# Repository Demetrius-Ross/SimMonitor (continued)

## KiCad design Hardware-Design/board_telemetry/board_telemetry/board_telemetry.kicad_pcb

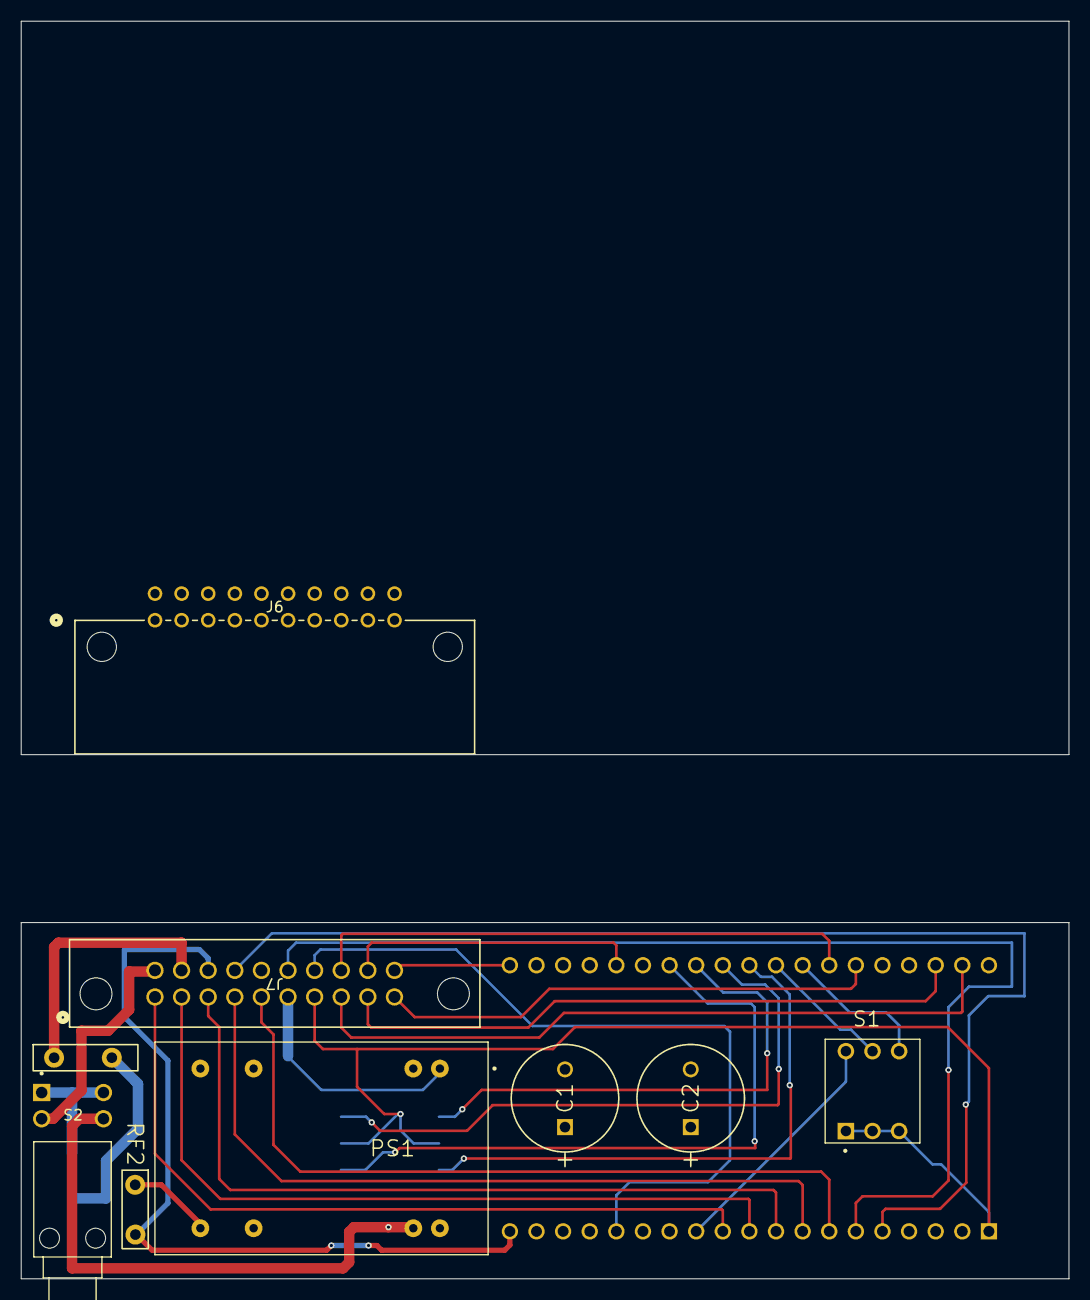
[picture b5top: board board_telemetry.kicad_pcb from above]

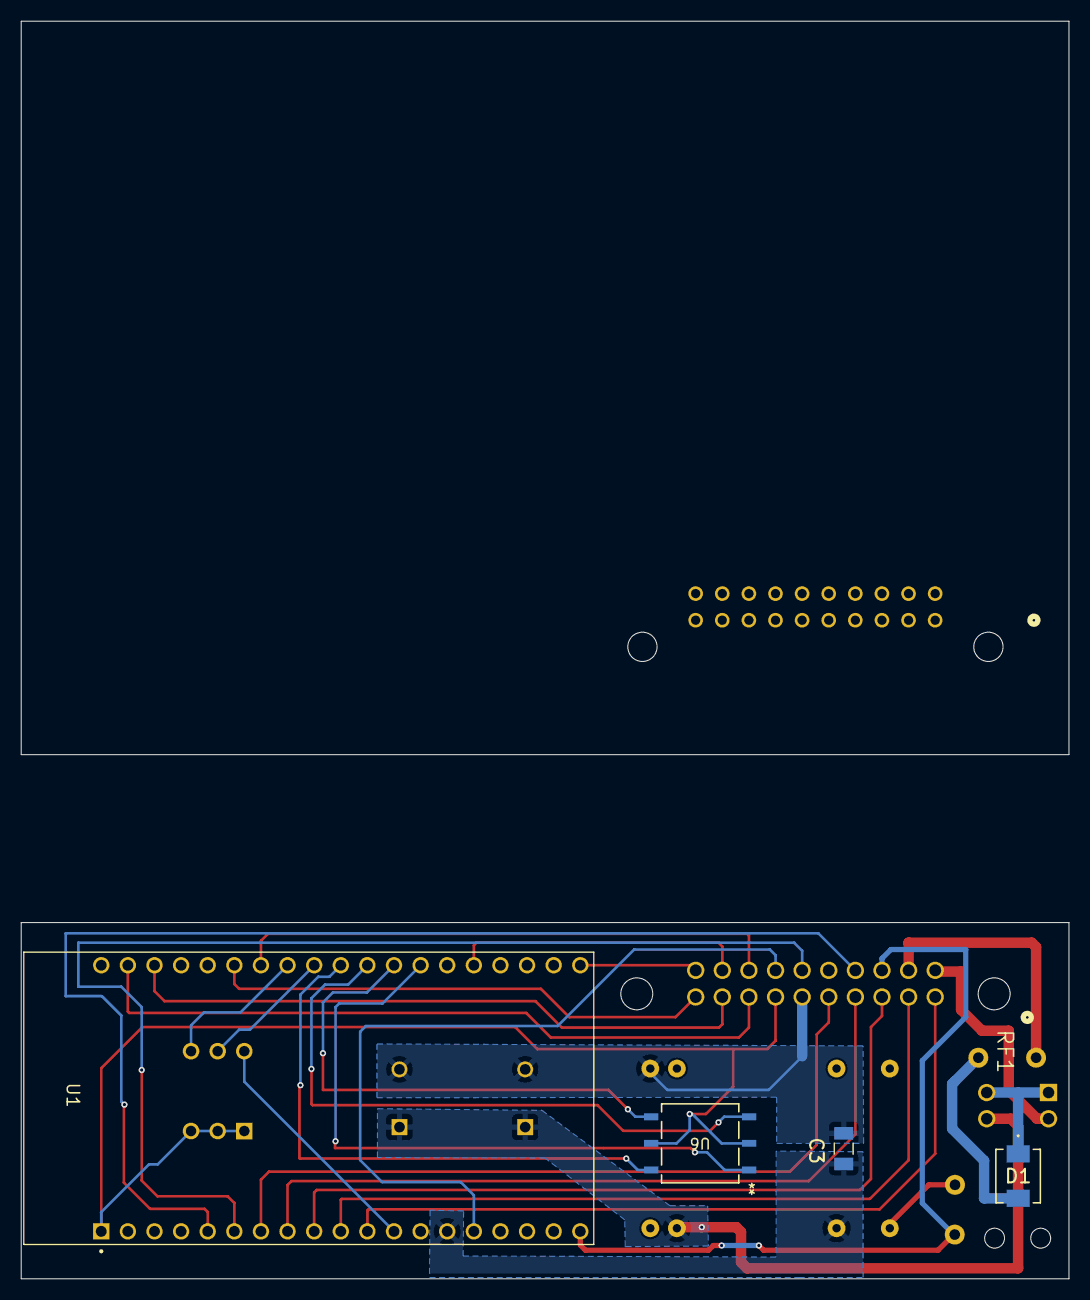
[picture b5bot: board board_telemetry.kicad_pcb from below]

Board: 2 copper layers, 100.0 x 34.0 mm, 13 parts (4 on the bottom side), 28 nets.

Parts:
C1, C2: UHE2A470MPD; PCAP_10x12_5-THRU-ELECT_NCA
C3: 1000pf/3kV; CAPC3216X180N
D1: SS34B-HF; DO214AASMB_CIP-L
J6: 20_pin_90
J7: 20-pin-straight; 20_pin_straight
PS1: REC5A-2405SW_H2; CONV_REC5A-2405SW_H2
RF1, RF2: PTC_RESET_FUSE
S1: DS01C-254-S-03BE; SW_DS01C-254-S-03BE
S2: PB400EEQR1BLK; SW_PB400EEQR1BLK
U1: ESP32-DEVKITC-32D; MODULE_ESP32-DEVKITC-32D
U6: SH-7070TB; SH-7070TB_7P1X7P3_NDC

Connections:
+3.3V: J6.B7, J7.7, S1.1A, S1.2A, S1.3A, U1.J2-1 (3V3), U6.2, U6.5
+24V: D1.1, S2.1, S2.3
+VIN: C1.1, C2.1, D1.2, J6.A1, J7.11, PS1.22 (+VIN), RF1.2, S2.2, S2.4
+VIN-dc: J6.A2, J7.12, RF1.1
+VOUT_esp_signal: J6.A3, J7.13, RF2.2, U1.J2-19 (EXT_5V)
-Vin: C1.2, C2.2, C3.2, J6.B6, J7.6, PS1.2 (-VIN)
/+VOUT: PS1.14 (+VOUT), RF2.1
CLK: J6.A10, J7.20, U1.J3-19 (CLK)
ESP_GND2: C3.1, J6.A8, J7.18, PS1.16 (-VOUT), U1.J2-14 (GND1), U1.J3-1 (GND3), U1.J3-7 (GND2)
GPIO_2: J6.A9, J7.19, U1.J3-15 (IO2)
GPIO_4: U1.J3-13 (IO4), U6.1
GPIO_5: U1.J3-10 (IO5), U6.6
GPIO_13: J6.A7, J7.17, U1.J2-15 (IO13)
GPIO_14: S1.1B, U1.J2-12 (IO14)
GPIO_16: U1.J3-12 (IO16), U6.4
GPIO_17: U1.J3-11 (IO17), U6.3
GPIO_18: S1.2B, U1.J3-9 (IO18)
GPIO_19: S1.3B, U1.J3-8 (IO19)
GPIO_21: J6.B10, J7.10, U1.J3-6 (IO21)
GPIO_22: J6.B9, J7.9, U1.J3-3 (IO22)
GPIO_23: J6.B8, J7.8, U1.J3-2 (IO23)
GPIO_25: J6.B3, J7.3, U1.J2-9 (IO25)
GPIO_26: J6.B2, J7.2, U1.J2-10 (IO26)
GPIO_27: J6.B1, J7.1, U1.J2-11 (IO27)
GPIO_32: J6.B5, J7.5, U1.J2-7 (IO32)
GPIO_33: J6.B4, J7.4, U1.J2-8 (IO33)
GPIO_ANAG_34: J6.A4, J7.14, U1.J2-5 (IO34)
GPIO_ANAG_35: J6.A6, J7.16, U1.J2-6 (IO35)

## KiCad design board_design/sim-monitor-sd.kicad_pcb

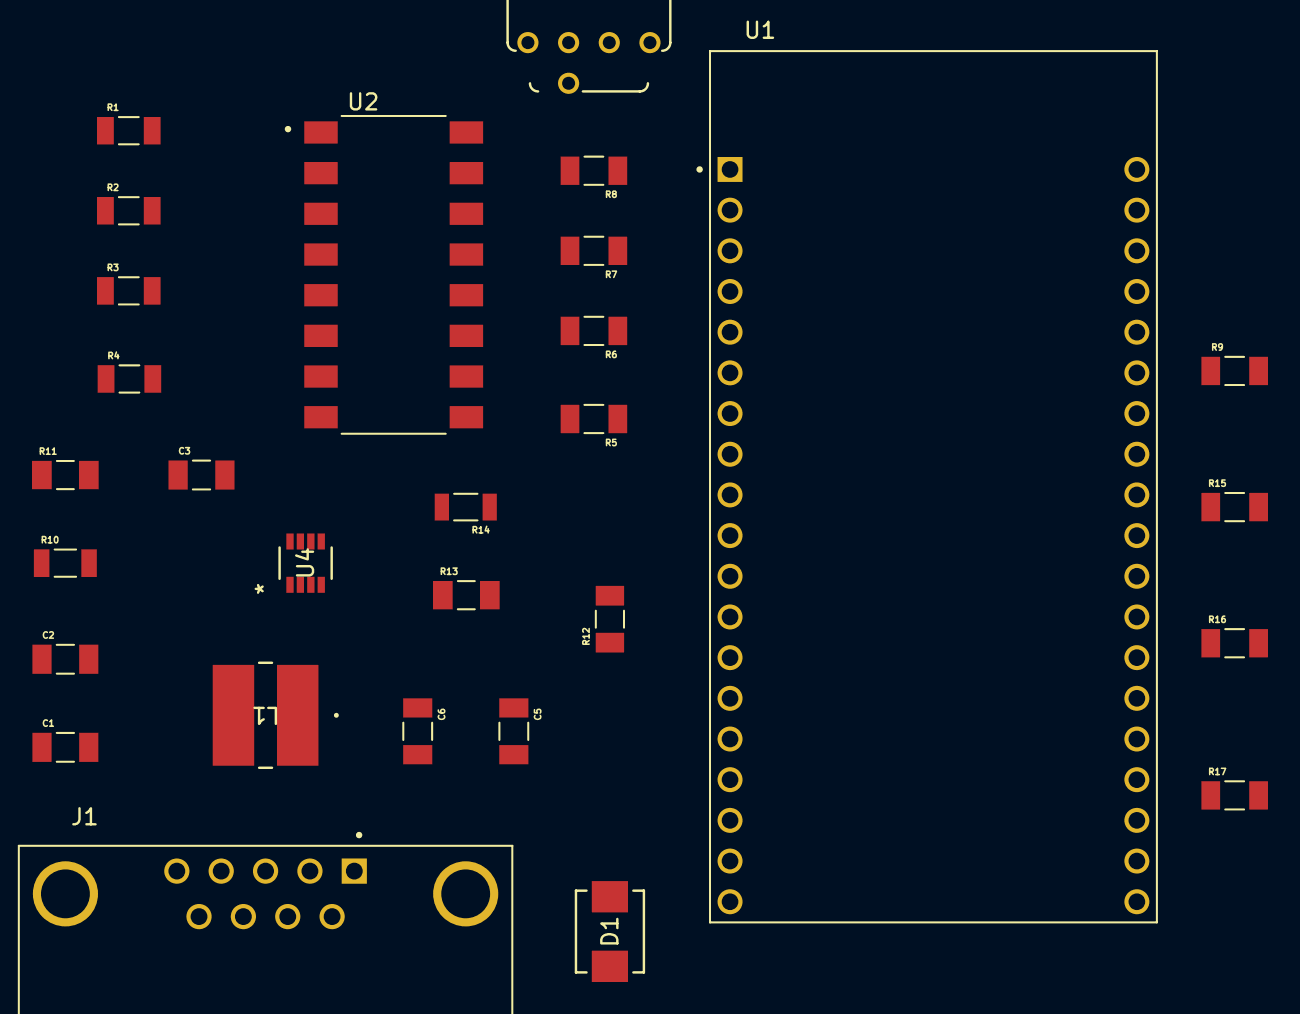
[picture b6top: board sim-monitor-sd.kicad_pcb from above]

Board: 2 copper layers, 29 parts (0 on the bottom side), 22 nets, no tracks yet.

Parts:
C1, C5, C6: CL31A226KAHNNNE; CAPC3216X180N
C2, C3: CL31B106KAHNNNE; CAPC3216X180N
D1: SS34B-HF; DO214AASMB_CIP
J1: A-DF_09_A_KG-T4S; ASSMANN_A-DF_09_A_KG-T4S
L1: HPC6045NC-4R7M; IND_HPC6045NC_TTA
R1, R2, R3, R4: CRGCQ1206F2K2; RESC3115X65N
R5, R6, R7, R8, R9, R15, R16, R17: CR1206-FX-1002ELF; RESC3216X75N
R10: RC1206FR-07499KL; RESC3116X65N
R11: RMCF1206FT10R0; RESC3216X70N
R12: RMCF1206FT40K2; RESC3216X70N
R13: RMCF1206FT7K50; RESC3216X70N
R14: CRCW120620K0FKEAC; RESC3015X65N
S1: DRR3016; DRR3010
U1: ESP32-DEVKITC-32D; MODULE_ESP32-DEVKITC-32D
U2: LTV-846S; SOIC254P1016X460-16N
U4: MP2315SGJ-Z; TSOT23-8_MP2315S_MNP

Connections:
+3.3V: R5.2, R6.2, R7.2, R8.2, S1.C, U1.J2-1 (3V3), U2.10, U2.12, U2.14, U2.16
+5V: D1.1, R11.1, U1.J2-19 (EXT_5V), U4.5 (BST)
+24V: C1.1, C2.1, J1.1, J1.2, J1.3, J1.4, J1.5, R1.1, R2.1, R3.1, R4.1, R10.2, U4.2 (IN)
GND: C1.2, C2.2, C5.2, C6.2, J1.6, R9.1, R13.1, R15.2, R16.2, R17.2, U1.J2-14 (GND1), U1.J3-7 (GND2), U2.2, U2.4, U2.6, U2.8, U4.4 (GND)
unnamed: C3.1, R11.2
unnamed: C5.1, C6.1, D1.2, L1.1, R12.1
unnamed: R1.2, U2.1
unnamed: R2.2, U2.3
unnamed: R3.2, U2.5
unnamed: R4.2, U2.7
unnamed: R12.2, R13.2, R14.1
unnamed: R17.1, S1.1, U1.J3-15 (IO2)
unnamed: R16.1, S1.2, U1.J3-13 (IO4)
unnamed: R5.1, U1.J2-12 (IO14), U2.9
unnamed: R15.1, S1.4, U1.J3-12 (IO16)
unnamed: R9.2, S1.8, U1.J3-11 (IO17)
unnamed: R8.1, U1.J2-9 (IO25), U2.15
unnamed: R7.1, U1.J2-10 (IO26), U2.13
unnamed: R6.1, U1.J2-11 (IO27), U2.11
unnamed: R10.1, U4.6 (EN)
unnamed: R14.2, U4.8 (FB)
unnamed: C3.2, L1.2, U4.3 (SW)

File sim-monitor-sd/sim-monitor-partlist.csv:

Reference,Qty,Serial Number,Name,Value,Price Per,Price Total
"C1,C5,C6",3,CL31A226KAHNNNE,Ceramic Capacitor,22  µF,$0.26 ,$0.78 
"C2,C3",2,CL31B106KAHNNNE,Ceramic Capacitor,10 µF,$0.11 ,$0.22 
D1,1,SS34B-HF,Schottky Diode,40V @ 3A,$0.27 ,$0.27 
J1,1,A-DF 09 A/KG-T4S,D-SUB ,,$0.77 ,$0.77 
L1,1,HPC6045NC-4R7M,Shielded Wirewound Inductor,4.7 µH,$0.11 ,$0.11 
"R1,R2,R3,R4",4,CRGCQ1206F2K2,Chip Resistor 1206,2.2 kOhms,$0.10 ,$0.40 
"R5,R6,R7,R8,R9,R15,R16,R17",8,CR1206-FX-1002ELF,Chip Resistor 1206,10 kOhms,$0.10 ,$0.80 
R10,1,RC1206FR-07499KL,Chip Resistor 1206,499 kOhms,$0.10 ,$0.10 
R11,1,RMCF1206FT10R0,Chip Resistor 1206,10 Ohms,$0.10 ,$0.10 
R12,1,RMCF1206FT40K2,Chip Resistor 1206,40.2 kOhms,$0.10 ,$0.10 
R13,1,RMCF1206FT7K50,Chip Resistor 1206,7.5 kOhms,$0.10 ,$0.10 
R14,1,CRCW120620K0FKEAC,Chip Resistor 1206,20 kOhms,$0.10 ,$0.10 
S1,1,DRR3016,Rot Switch,16 Pos Hex,$3.09 ,$3.09 
U1,1,ESP32-DEVKITC-32D,ESP32,,,
U2,1,LTV-846S,Optocoupler,4-Channel,$1.07 ,$1.07 
U4,1,MP2315SGJ-Z,Buck Converter,,$2.92 ,$2.92 
,1,RA111C1021-116,On-Off Switch,,$1.57 ,$1.57 
,,,,,,
,,,,,,
,,,,,,
,,,,,,
,,,,,,
,,,,,,Total
,,,,,,$12.50

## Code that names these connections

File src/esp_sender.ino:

#include <esp_now.h>
#include <WiFi.h>

// Receiver ESP MAC Address (replace with your main ESP's MAC address)
uint8_t receiverMAC[] = {0x78, 0xE3, 0x6D, 0xDF, 0x69, 0x7C};

// Data structure to send
typedef struct {
  char simName[10]; // Simulator name
  int rampState;    // 0: In Motion, 1: Ramp Up, 2: Ramp Down
  int motionState;  // 1: Sim Down (Home), 2: Sim Up
  int status;       // 1: Connected, 0: No Data
} Message;

Message myData;

// Pin definitions for LEDs
#define RAMP_UP_PIN 14     // Ramp Up
#define RAMP_DOWN_PIN 27   // Ramp Down
#define SIM_HOME_PIN 26    // Sim at Home

void onSent(const uint8_t *mac_addr, esp_now_send_status_t status) {
  // Send callback, no extra logging to keep things clean
}

void setup() {
  Serial.begin(115200);

  // Initialize GPIO pins
  pinMode(RAMP_UP_PIN, INPUT);
  pinMode(RAMP_DOWN_PIN, INPUT);
  pinMode(SIM_HOME_PIN, INPUT);

  // Set simulator name
  strcpy(myData.simName, "PC-12");

  // Initialize Wi-Fi
  WiFi.mode(WIFI_STA);

  // Initialize ESP-NOW
  if (esp_now_init() != ESP_OK) {
    Serial.println("Error initializing ESP-NOW");
    return;
  }

  // Register send callback
  esp_now_register_send_cb(onSent);

  // Register peer
  esp_now_peer_info_t peerInfo;
  memcpy(peerInfo.peer_addr, receiverMAC, 6);
  peerInfo.channel = 0; // Default channel
  peerInfo.encrypt = false;

  if (esp_now_add_peer(&peerInfo) != ESP_OK) {
    Serial.println("Failed to add peer");
    return;
  }

  Serial.println("Sender ESP ready to send messages.");
}

void loop() {
  // Read states from the input pins
  int rampUp = digitalRead(RAMP_UP_PIN);
  int rampDown = digitalRead(RAMP_DOWN_PIN);
  int simHome = digitalRead(SIM_HOME_PIN);

  // Determine ramp state
  if (rampUp == HIGH && rampDown == HIGH) {
    myData.rampState = 0; // In Motion
  } else if (rampUp == LOW) {
    myData.rampState = 1; // Ramp Up
  } else if (rampDown == LOW) {
    myData.rampState = 2; // Ramp Down
  } else {
    myData.rampState = 0; // Default to "In Motion" if no valid state is detected
  }

  // Determine motion state
  myData.motionState = (simHome == LOW) ? 1 : 2; // 1: Sim Down (Home), 2: Sim Up

  // Determine status
  myData.status = (rampUp || rampDown || simHome) ? 1 : 0; // 1: Connected, 0: No Data

  // Send data via ESP-NOW
  esp_err_t result = esp_now_send(receiverMAC, (uint8_t *)&myData, sizeof(myData));

  delay(2000); // Send data every 2 seconds
}

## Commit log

2024-12-02 ESP communication update
2024-12-02 ESP communication update 2
2024-12-03 ESP communication update 3
2024-12-03 led update
2024-12-04 Monitor Update w/ GUI
2024-12-04 Pin Update
2024-12-12 invert led
2024-12-12 office build
2024-12-15 OTA Update
2024-12-16 OTA Update 2
2024-12-17 serial monitor Update 2
2024-12-17 serial monitor Update 2.1
2024-12-18 added old files
2025-02-17 Relay Update
2025-02-17 micro-python update
2025-02-17 micro-python update v1
2025-02-17 micro-python update v2
2025-02-17 micro-python update v3
2025-02-17 micro-python update v4
2025-02-17 deploy update
2025-02-17 sender fix
2025-02-17 sender fix v01
2025-02-17 sender fix v02
2025-02-17 name fix
2025-02-17 sh fix
2025-02-19 monitoring update
2025-02-20 receiver update
2025-02-21 sender update
2025-02-21 V2 Update
2025-02-25 gui update
2025-02-26 V3 Update
2025-03-01 kiCad
2025-03-05 3Mar
2025-03-06 buck converter update
2025-03-06 6Mar
2025-03-07 7Mar
2025-03-08 8Mar
2025-03-11 pcb update
2025-03-19 images
2025-04-04 updated schematics
2025-04-04 schematic update
2025-04-05 updated schematic
2025-04-12 PCB updated
2025-04-15 updating board
2025-05-06 board update
2025-05-21 id updates
2025-05-23 image update
2025-05-23 debug update
2025-06-05 updated gui
2025-06-12 serial update
2025-07-10 Status Update
2025-07-10 ID Fix
2025-07-16 status
2025-11-06 Board MKIV init
2025-11-12 telemetry
2025-11-12 update telemetry
2025-11-13 updata
2025-11-29 MKIV Update
2025-11-30 GUI DB Update
2025-12-18 tele
2026-01-03 Jan Update
